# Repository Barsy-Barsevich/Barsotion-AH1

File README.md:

# AH1 development module for ICM-42688-P & BMP388
- Allows to communicate with ICM-42688-P via SPI and I2C
- Allows to communicate with BMP388 via I2C
## Libraries
- [Barsotion ICM-42688-P C-driver](https://github.com/Barsy-Barsevich/ICM42688_Barsotion)
- [Barsotion BMP388 Arduino library](https://github.com/Barsy-Barsevich/BMP388_Barsotion)

## The next devboard of AHx series
- [Barsotion AH2 - ESP32-S3 & ICM-42688-P connection devboard](https://github.com/Barsy-Barsevich/Barsotion-AH2)

## Topology

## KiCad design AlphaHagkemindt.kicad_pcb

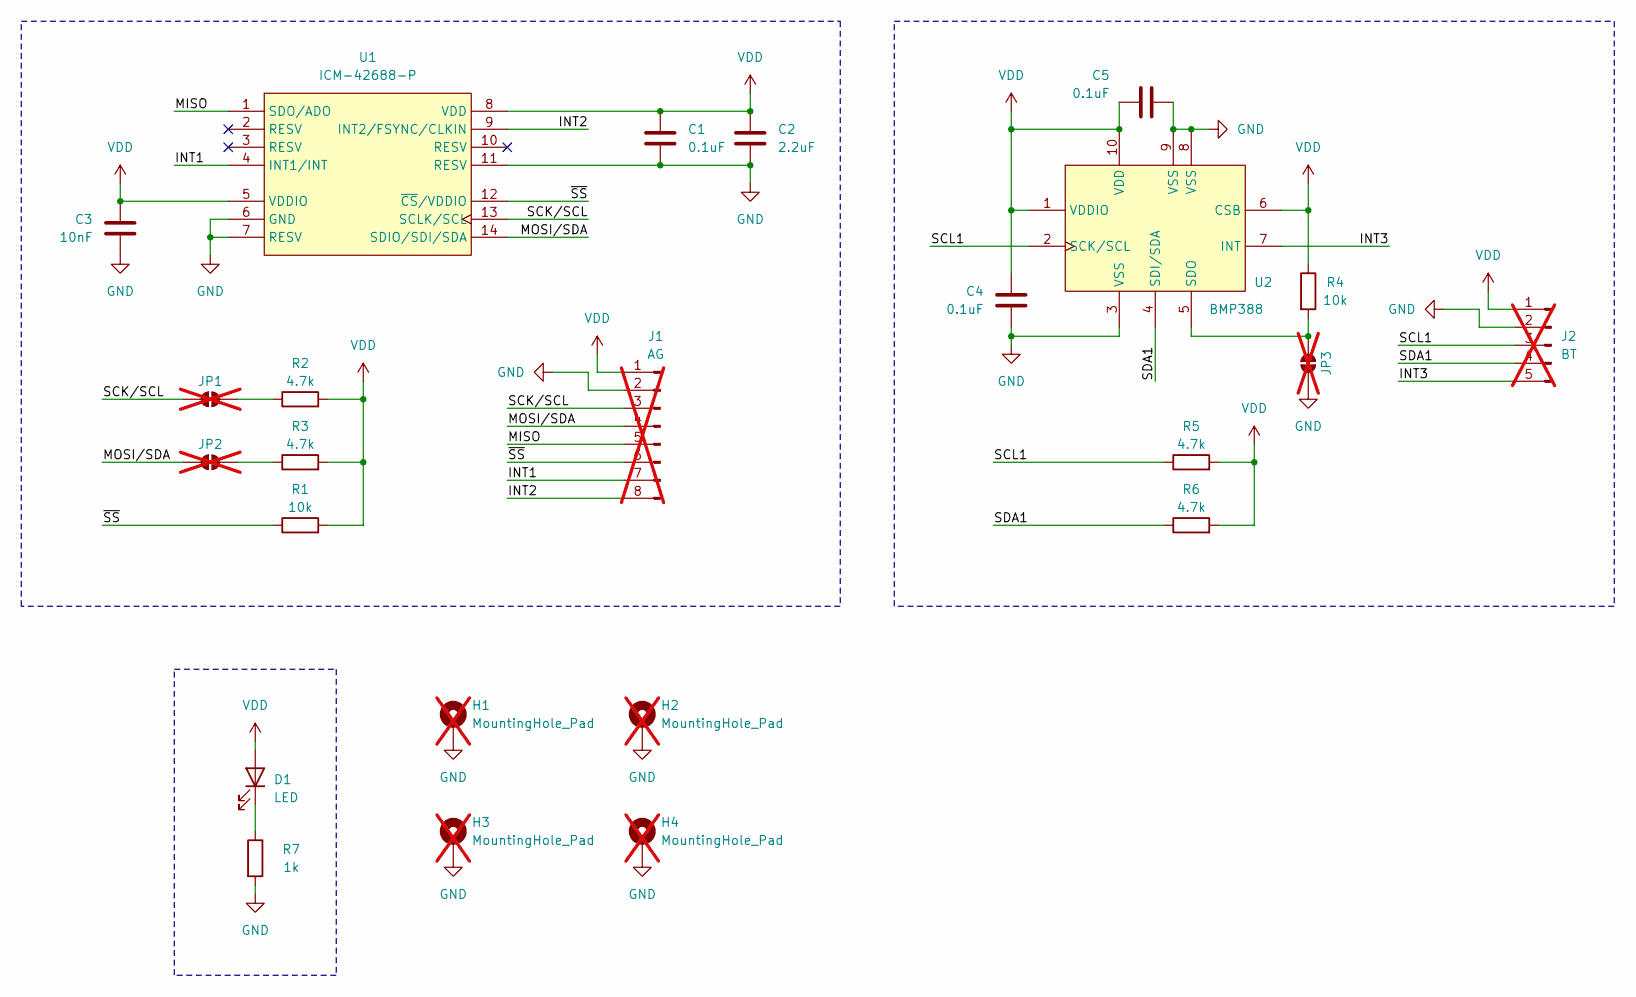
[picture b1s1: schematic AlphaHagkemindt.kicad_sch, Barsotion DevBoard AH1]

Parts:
C1, C4, C5: 0.1uF; C_0603_1608Metric
C2: 2.2uF; C_0603_1608Metric
C3: 10nF; C_0603_1608Metric
D1: LED; LED_0603_1608Metric
H1, H2, H3, H4: MountingHole_Pad; MountingHole_2.7mm_Pad_Via; not fitted
J1: AG; PinHeader_1x08_P2.54mm_Vertical; not fitted
J2: BT; PinHeader_1x05_P2.54mm_Vertical; not fitted
JP1, JP2, JP3: SolderJumper_2_Open; SolderJumper-2_P1.3mm_Open_RoundedPad1.0x1.5mm; not fitted
R1, R4: 10k; R_0603_1608Metric
R2, R3, R5, R6: 4.7k; R_0603_1608Metric
R7: 1k; R_0603_1608Metric
U1: ICM-42688-P; LGA-14_3x2.5mm_P0.5mm_LayoutBorder3x4y
U2: BMP388; ST_HLGA-10_2x2mm_P0.5mm_LayoutBorder3x2y

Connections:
/INT1: J1.7, U1.4 (INT1/INT)
/INT2: J1.8, U1.9 (INT2/FSYNC/CLKIN)
/INT3: J2.5, U2.7 (INT)
/MISO: J1.5, U1.1 (SDO/ADO)
/MOSI/SDA: J1.4, JP2.1 (A), U1.14 (SDIO/SDI/SDA)
/SCK/SCL: J1.3, JP1.1 (A), U1.13 (SCLK/SCL)
/SCL1: J2.3, R5.1, U2.2 (SCK/SCL)
/SDA1: J2.4, R6.1, U2.4 (SDI/SDA)
/~SS: J1.6, R1.1, U1.12 (~CS/VDDIO)
GND: C1.2, C2.2, C3.2, C4.2, C5.1, H1.1, H2.1, H3.1, H4.1, J1.2, J2.2, JP3.2 (B), R7.2, U1.6 (GND), U1.7 (RESV), U1.11 (RESV), U2.3 (VSS), U2.8 (VSS), U2.9 (VSS)
unnamed: D1.1 (K), R7.1
unnamed: JP1.2 (B), R2.1
unnamed: JP2.2 (B), R3.1
unnamed: JP3.1 (A), R4.2, U2.5 (SDO)
VDD: C1.1, C2.1, C3.1, C4.1, C5.2, D1.2 (A), J1.1, J2.1, R1.2, R2.2, R3.2, R4.1, R5.2, R6.2, U1.5 (VDDIO), U1.8 (VDD), U2.1 (VDDIO), U2.6 (CSB), U2.10 (VDD)

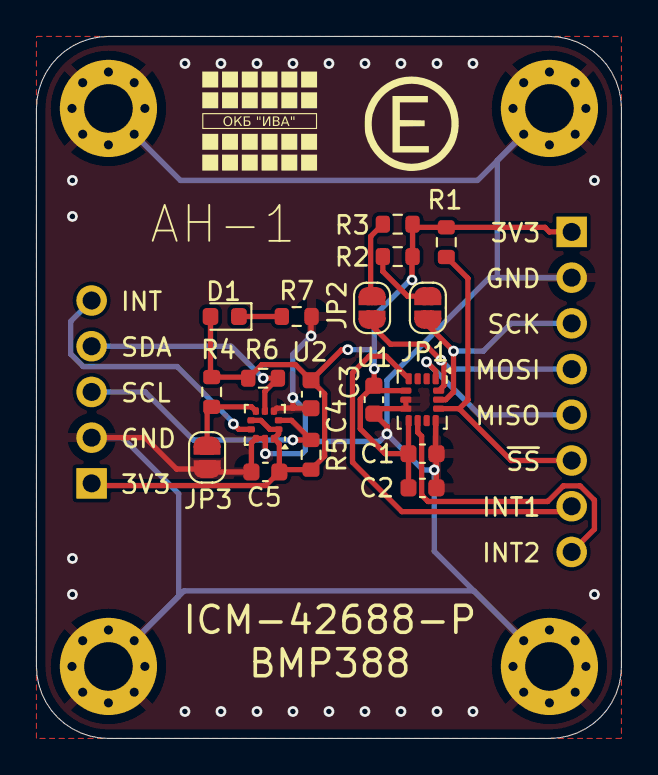
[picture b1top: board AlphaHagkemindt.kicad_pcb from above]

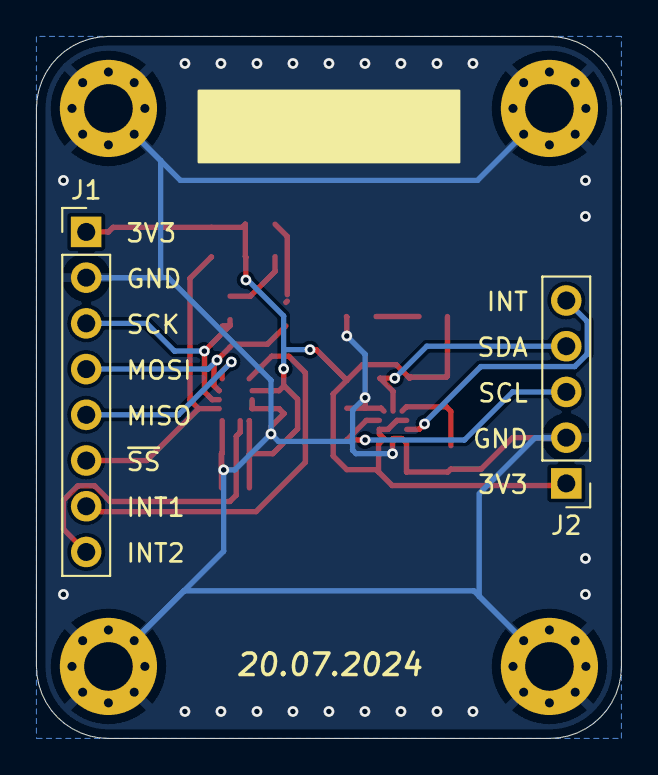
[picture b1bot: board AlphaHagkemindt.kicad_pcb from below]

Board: 2 copper layers, 32.5 x 39.0 mm, 24 parts (2 on the bottom side), 15 nets.

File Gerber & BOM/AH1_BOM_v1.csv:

Reference,Value,Datasheet,Description,Footprint,Qty,DNP
C3,10nF,~,Unpolarized capacitor 0603 X7R,Capacitor_SMD:C_0603_1608Metric,1,
C2,2.2uF,~,Unpolarized capacitor 0603 X7R,Capacitor_SMD:C_0603_1608Metric,1,
"C1,C4,C5",0.1uF,~,Unpolarized capacitor 0603 X7R,Capacitor_SMD:C_0603_1608Metric,3,
R7,1k,~,Resistor 0603,Resistor_SMD:R_0603_1608Metric,1,
"R2,R3,R5,R6",4.7k,~,Resistor 0603,Resistor_SMD:R_0603_1608Metric,4,
"R1,R4",10k,~,Resistor 0603,Resistor_SMD:R_0603_1608Metric,2,
D1,LED,~,"Light emitting diode, green 0603",LED_SMD:LED_0603_1608Metric,1,
U1,ICM-42688-P,https://invensense.tdk.com/wp-content/uploads/2020/04/ds-000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,InvenSense High-precision 6-axes gyroscope accelerometer,Package_LGA:LGA-14_3x2.5mm_P0.5mm_LayoutBorder3x4y,1,
U2,BMP388,https://pdf1.alldatasheet.com/datasheet-pdf/download/1132070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,Bosch barometer thermometer,Package_LGA:ST_HLGA-10_2x2mm_P0.5mm_LayoutBorder3x2y,1,

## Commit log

2025-03-06 gitignore add
2025-03-06 Create LICENSE
2025-04-23 topology photoes added
